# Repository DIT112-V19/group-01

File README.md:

# group-01

## README

## Contents of the readme
1. Project description
2. Installation
3. User manual
4. The PCB
5. The video

### 1. Project description of Speedy Carzales Arduino Alarm Car
Speedy Carzales is a smartcar, that plays a tone on a certain time, while it drives away from the user and tries to avoid obstacles as well as being turned off.
Another functionality is the ability to manually operate it.
The project consists of the Android App and the Arduino Code.
The App is optimized for Android 9.0. 

The hardware, used in this project is:
* Arduino Mega
* 4 Motors
* Smartcar Shield
* 2 Ultrasonic Sensors
* Active Buzzor
* Custom made PCB
* a button (Pullup Configuration)
* a Gyroscope (no code for its implementation used)
* 2 Odometers
* On/Off Switch
* 8 Batteries and a Batterie 
* 1 Battery Snap Connector
* 1 Battery Clip (8 * AA Battery)
* 1 Resistor
* a variety of jumpers, and cables fitting to the hardware
* 4 tires
* acrylic board as platform for the car
* Bluetooth Module
* 1 Mini-Breadboard

Tools needed to assemble the car
* Hot Glue Gun
* Screwdriver
* Soldering Iron
* surge protector*

*Please keep in mind to connect the surge protector with your computer when you plug your arduino in your USB Port. We take no resonsiblity for damage to your hardware, body or any other involved subjects.

## 2. Installation
1. Download arduino IDE, make sure that the arduino board is connected through a cable
2. Download android studio IDE
3. Import the code onto your computer
4. Upload the code into the arduino using the arduino IDE
5. Upload the android application on an android device using the android studio IDE

## 3. User manual 
1. Turn on the car with the On/Off switch located on the side 
2. Boot the phone application
3. Press connect on the welcome page
4. Use the on/off button to turn on your bluetooth 
5. Press discover to find bluetooth devices
6. Choose your device on the list by tapping on it
7. Press "start connection"
8. After getting the message "successfully connected" popped up, press "continue"
9. Choose between setting the alarm or play with the car 
10. "play" : Control the car by pressing the buttons (if "reconnect bluetooth" appears, please reconnect)
11. "Alarm" : Set the alarm by choosing the time on the clock provided. Then click "set alarm" 
12. "Alarm" : Press activate to immediately set off the alarm
13. To return at any point in the app, use the return button in the upper left corner
14. ##### Enjoy ! 

## 4. The PCB
The PCB was designed in EAGLE CAD. It is used to connect the Ultrasonic Sensors to the Arduino, as well as the button. The cutouts are fitted so it will be able to sit on the smartcarshield, without blocking the Gyroscope or the connections. 

## 5. The video
Link: https://www.youtube.com/watch?v=jtvX933osug

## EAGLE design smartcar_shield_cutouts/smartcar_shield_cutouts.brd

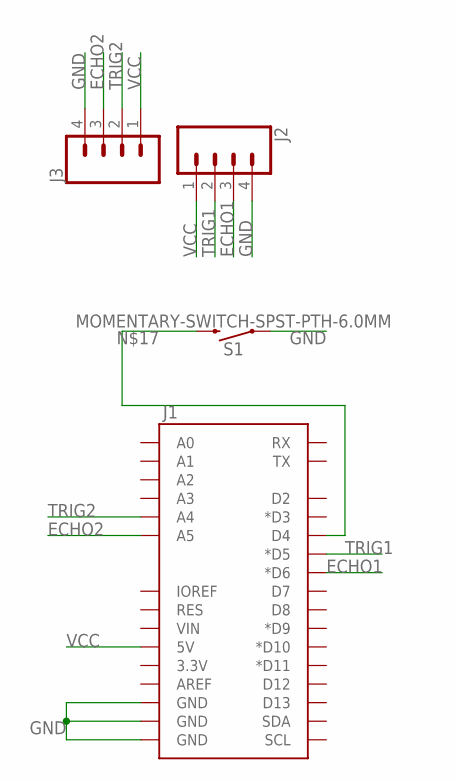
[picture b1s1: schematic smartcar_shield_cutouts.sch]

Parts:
J1: ARDUINO_R3_SHIELDUNO_R3_SHIELD_LOCK; UNO_R3_SHIELD_LOCK
J2, J3: CONN_04; 1X04
S1: MOMENTARY-SWITCH-SPST-PTH-6.0MM; TACTILE_SWITCH_PTH_6.0MM

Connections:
ECHO1: J1.D6 (*D6), J2.3
ECHO2: J1.A5, J3.3
GND: J1.GND@0 (GND), J1.GND@1 (GND), J1.GND@2 (GND), J2.4, J3.4, S1.1
unnamed: J1.D4, S1.3 (2)
TRIG1: J1.D5 (*D5), J2.2
TRIG2: J1.A4, J3.2
VCC: J1.5V, J2.1, J3.1

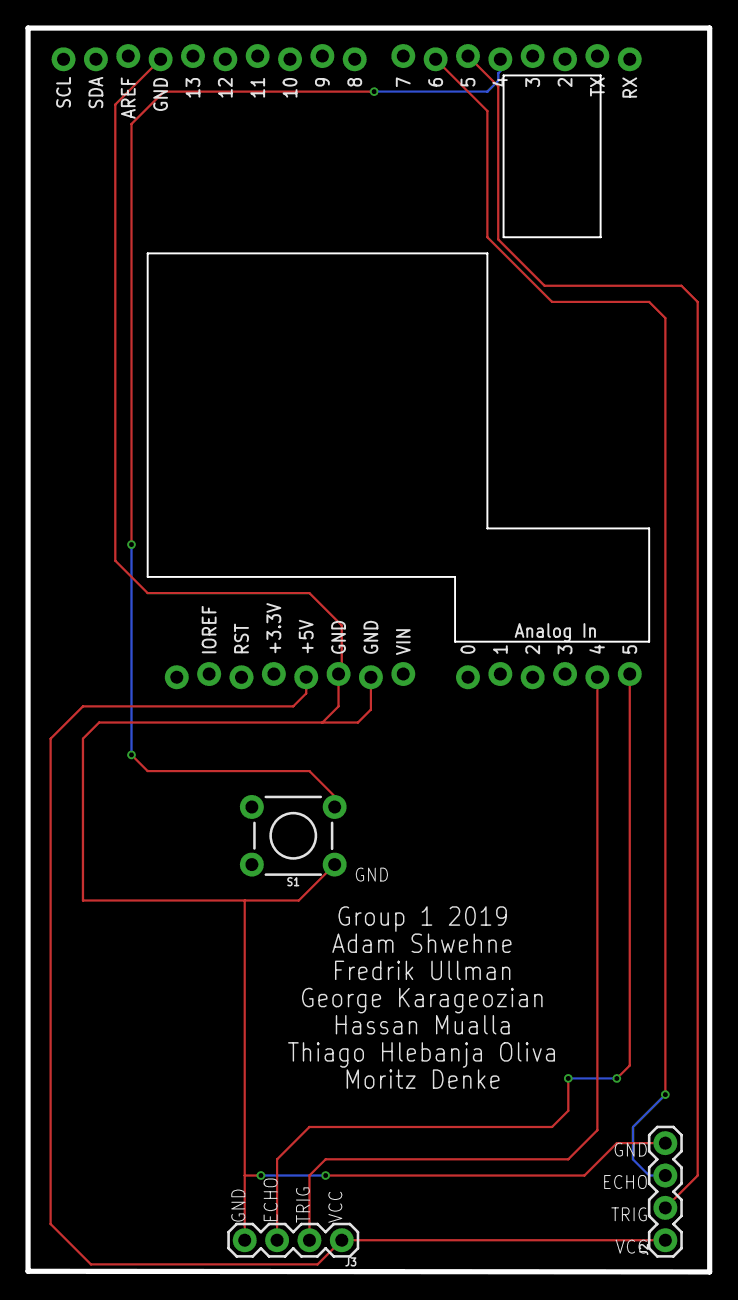
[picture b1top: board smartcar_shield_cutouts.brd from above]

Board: 2 copper layers, 53.5 x 97.7 mm, 4 parts (0 on the bottom side), 7 nets.

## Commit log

2019-04-02 Updating readme with project proposal
2019-04-03 Basic Obstacle Avoidance Sketch
2019-04-08 Improved Obstacle Avoidance
2019-04-08 Updated readme
    Added proper markup and removed the idea of using MIT app inventor
2019-04-10 Add templates
2019-04-11 Car manual control via bluetooth
2019-04-11 fixed changes requested
2019-04-11 basic obstacle avoidance
2019-04-11 basic obstacle avoidance changed error
2019-04-12 change if/else statement to switch
2019-04-12 correct the code
2019-04-12 small update on the BT Manual Switch case, changing default case to fix bug
2019-04-12 changing default case in switch statement
2019-04-12 cleaned white spaces and minor fix on the switch case
2019-04-12 basic android app build after tutorial and slightly modified
2019-04-16 I have deleteed the bluetooth folder
2019-04-16 Basic Bluetooth App co authored by George, Fredrik, Adam, Hassan, Thiago
2019-04-19 drive car in two directions using app
2019-04-19 Option to click the button 'play' to start operating the car
2019-04-22 left arrow icon and functionality added
2019-04-22 added right button and functionality
2019-04-25 created setting the alarm button
2019-04-25 Added connect button to frontpage
2019-04-25 improved design and added connect button
2019-04-26 new branch to work on obstacle avoidance with SmartCar. Also, basic configuration of SmartCar
2019-04-28 moved methods for operating car to fix bug
2019-04-28 Unneccesary commented out code removed
2019-04-28 Car control divided in methods
    The methods are divided for easier interpretation and understanding, commnets were added too.
    Loop stil has to be fixed for obstacle avoidance.
2019-04-28 fixed spacing. Still working on the loop
2019-04-29 added method to randomly choose random number and fixed method for random direction
2019-04-29 Improved obstacle avoidance functionality complete, with Differential Control, and with random behavior when avoiding obstacles
2019-04-29 Minor fix
    I had set the sensor Max Distance to 35 and have just adjusted it to 30 (35 was causing minor bugs)
2019-04-30 connecting data between activities
2019-04-30 added mainmenu button in connectActivity
2019-04-30 I made the write-function static, to be able to reference it from everywhere in the application
2019-05-04 added a welcome page & general clean-up
2019-05-06 added interrupt to make the car stop when the button is pressed(pre-tested)
2019-05-07 removed the delays and implemented a system based on millis() instead
2019-05-07 changed the way the car turns to a more curve driving way, instead of tank style
2019-05-09 added method displayDistances()
2019-05-09 deleted unnecessary folder multipleSensors
2019-05-09 assigning variables to 0
2019-05-09 initial MP3 shield code from template
2019-05-10 removed sketch outisde of folder and added button (not working so far)
2019-05-10 added the PCB design
2019-05-10 implemented pullup button
2019-05-12 added toastMessages function and implementation to a couple of methods in BluetoothConnectionService
2019-05-13 toastmessages added to bluetooth connection
2019-05-13 implemented the button and updated the pcb design
2019-05-13 changed pin 4 to A4
2019-05-13 refactoring and adding activate button
2019-05-13 merging obstacle avoidance with manual control and doing necessary changes for android app
2019-05-14 styling the landing page by adding colorful background and button
2019-05-14 styling the app layout
2019-05-14 manual control and alarm obstacle avoidance integrated
2019-05-14 styling the whole app layout
2019-05-15 added return buttons
2019-05-15 prevent app from crashing
2019-05-15 bug fixes and reformat buttons
2019-05-15 added comments for readability
2019-05-15 added all text into strings.xml
2019-05-15 started alarm functionality implementation
2019-05-15 implementation of a timecontrolled function to send a signal to the arduino
2019-05-17 fixed the issue with hour recognition
2019-05-17 alarm is working now
2019-05-17 alarm functionality works, but keeps sending f constantly
2019-05-17 implemented a boolean that stops the app from sending f constatnly
2019-05-19 Refactoring Android code
    Initail commit, Main changes:
    -Removed redundent casting
    -Added comments on code
2019-05-20 changed pins accordingly
2019-05-20 Refactoring app
    removed redundant casting
2019-05-20 Broke down main loop into smaller methods
2019-05-20 renamed variables and added comments
2019-05-20 fixed change if statement in automaticObstacleAvoidance method so that button stops the car also when it's turning around
2019-05-20 reorganized declaration of variables and improved comments
2019-05-20 updated button pin configuration to match that of the Master Branch
2019-05-20 Adding basic buzzer code to mergingArduino
2019-05-20 fixed layout
2019-05-20 visual framework design
2019-05-20 aligned the play buttons better
2019-05-20 set visual framework
2019-05-20 added features to buttons
2019-05-20 fixed listview color, set to white
2019-05-20 bugfix of listview
2019-05-21 Initial commit, integrate second ultrasonic sensor
2019-05-21 fixed bug whileloop
2019-05-21 I fixed the arduino code
2019-05-21 Initial Buzzer implementation
2019-05-21 Implementing buzzer
2019-05-23 refactoring of class file names
2019-05-23 added text to strings.xml & indentation of code
2019-05-23 uppercase letter
2019-05-23 max 25 devices on arraylist
2019-05-23 implemented basic function for the rear sensor
2019-05-23 improved functionality of the rear sensor
2019-05-23 added comments and finished the basic functionality for the rear sensor
2019-05-23 cleaned up the code and removed unnecessary measurement methods
2019-05-24 refresh button added
2019-05-27 added Documentation Folder and made Project-Proposal file
2019-05-27 Update README.md
    Updated user manual
2019-05-27 Deleted the refresh button in activity_start_connection.xml and related code in java
2019-05-27 Added presentation as pdf
2019-05-27 presentation upload
2019-05-27 Deleted reundant files and lines of code

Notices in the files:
parts and their libraries:
SparkFun-Boards: Licensing: Creative Commons ShareAlike 4.0 International - https://creativecommons.org/licenses/by-sa/4.0
